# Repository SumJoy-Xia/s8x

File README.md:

# s8x
open source H87/H88 and infinite875 PCB made by sumjoy
开源H87/H88和infinite875 PCB

kicad preview
kicad预览图

firmware to be updated, stay tuned
固件后续更新

PYG.step is the step file of PCB which represents the 3d model of PCB
in case u need it for drawing keyboard cases
PYG.step是PCB的模型
为了方便大家画键盘

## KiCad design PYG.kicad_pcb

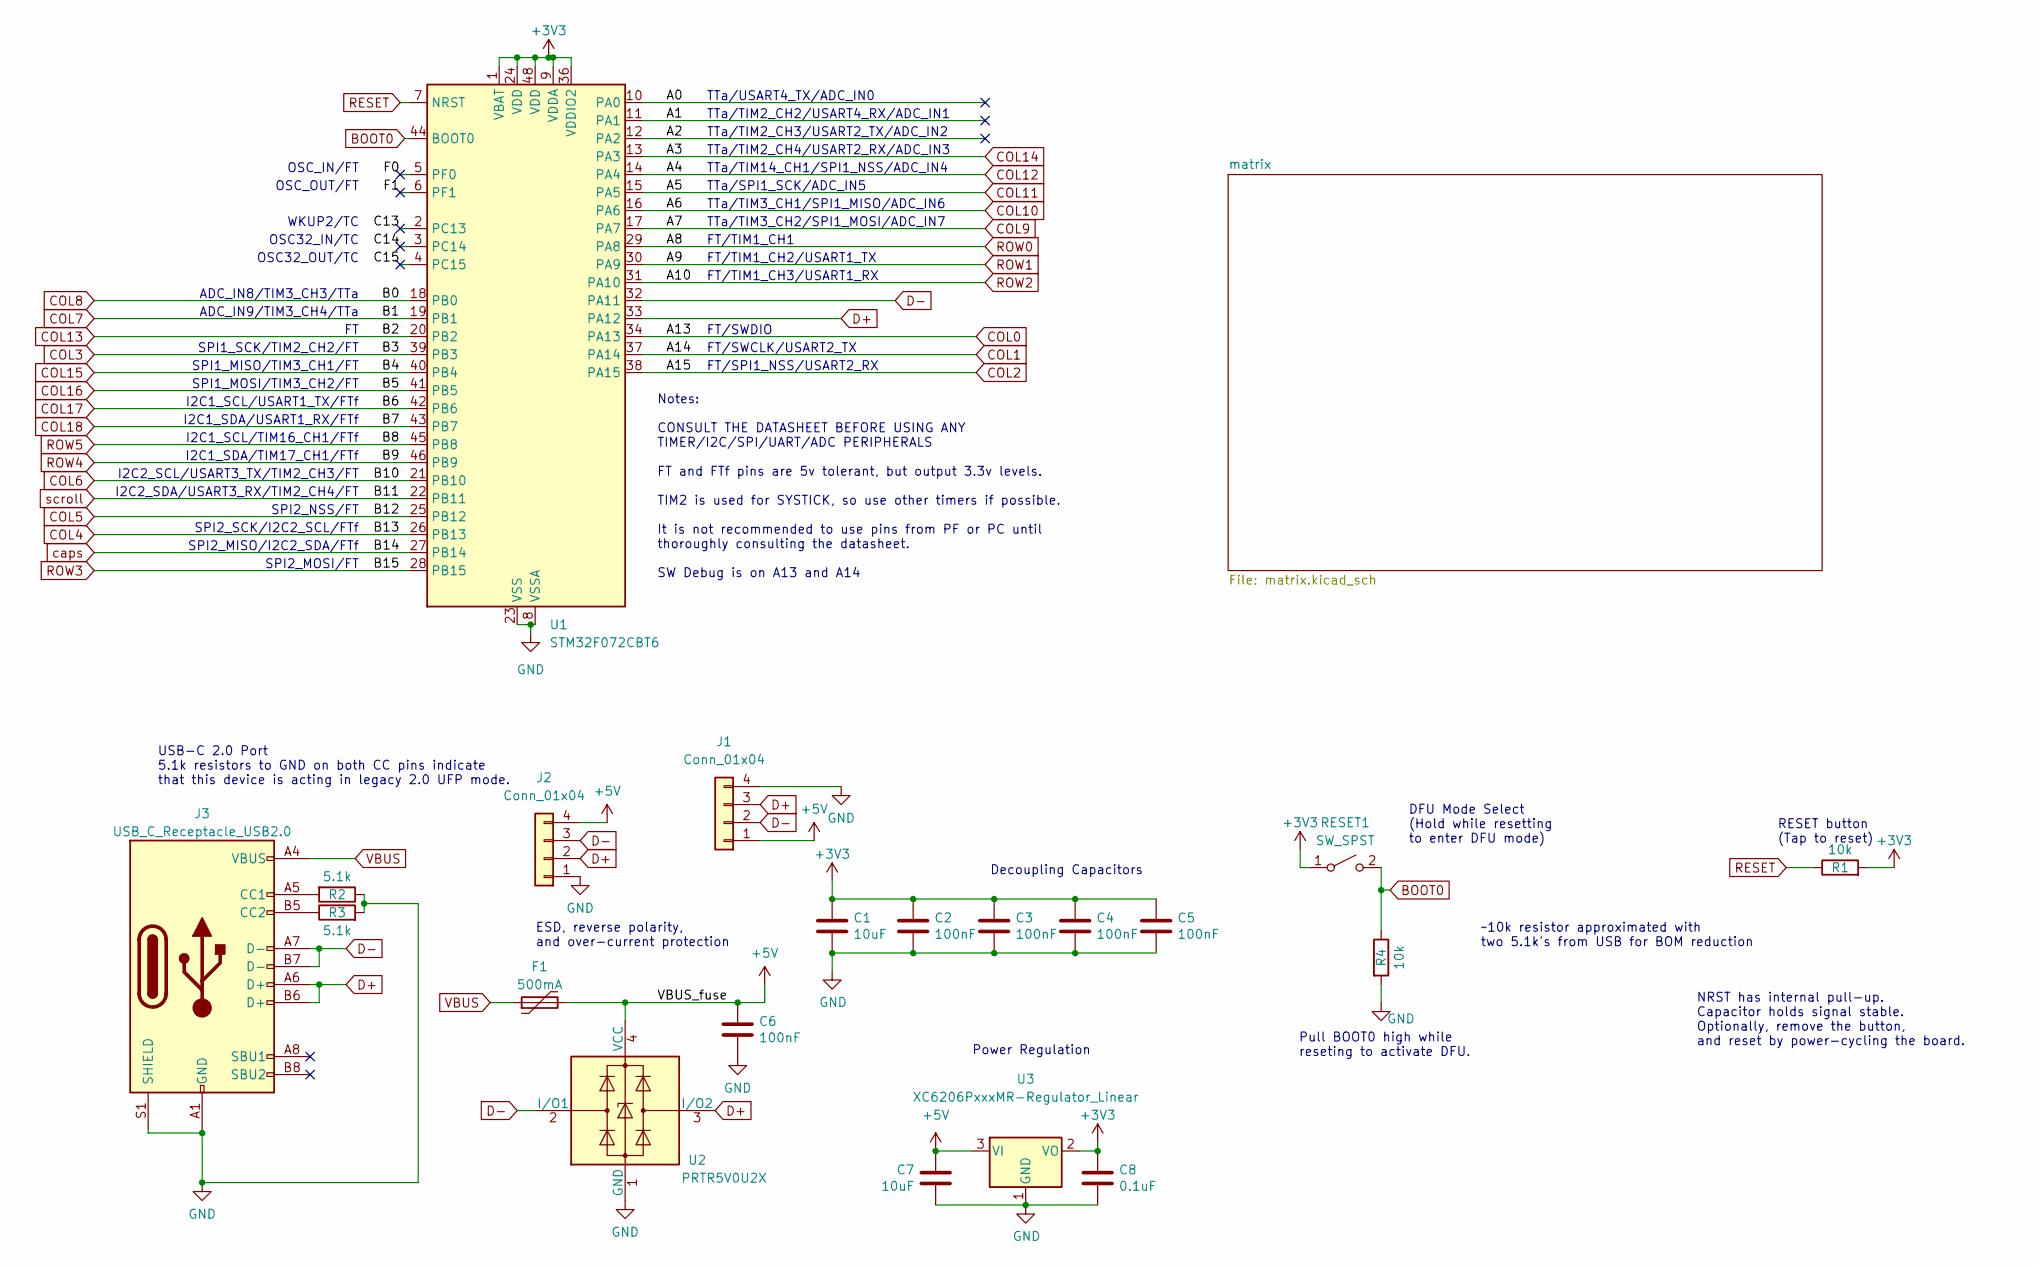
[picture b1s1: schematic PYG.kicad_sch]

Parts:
C1, C7: 10uF; C_0805_2012Metric; LCSC C307331
C2, C3, C4, C5, C6: 100nF; C_0805_2012Metric; LCSC C307331
C8: 0.1uF; C_0805_2012Metric; LCSC C307331
F1: 500mA; Fuse_1206_3216Metric; LCSC C135341
J1: Conn_01x04; JST_SH_SM04B-SRSS-TB_1x04-1MP_P1.00mm_Horizontal
J2: Conn_01x04; PinHeader_1x04_P2.54mm_Vertical
J3: USB_C_Receptacle_USB2.0; USB_C_Receptacle_HRO_TYPE-C-31-M-12; JlcRotOffset 180
R1, R4: 10k; R_0805_2012Metric
R2, R3: 5.1k; R_0805_2012Metric
RESET1: SW_SPST; SW_SPST_TL3342
U1: STM32F072CBT6; LQFP-48_7x7mm_P0.5mm; JlcRotOffset 90
U2: PRTR5V0U2X; SOT-143; LCSC C2827688
U3: XC6206PxxxMR-Regulator_Linear; SOT-23; LCSC C5446

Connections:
+3V3: C1.1, C2.1, C3.1, C4.1, C5.1, C8.1, R1.2, RESET1.1 (A), U1.1 (VBAT), U1.9 (VDDA), U1.24 (VDD), U1.36 (VDDIO2), U1.48 (VDD), U3.2 (VO)
+5V: C6.1, C7.1, F1.2, J1.1, J2.4, U2.4 (VCC), U3.3 (VI); also elsewhere on the board
/A0: U1.10 (PA0)
/A1: U1.11 (PA1)
/A2: U1.12 (PA2)
/C13: U1.2 (PC13)
/C14: U1.3 (PC14)
/C15: U1.4 (PC15)
/F0: U1.5 (PF0)
/F1: U1.6 (PF1)
BOOT0: R4.1, RESET1.2 (B), U1.44 (BOOT0)
COL0: U1.34 (PA13); also elsewhere on the board
COL1: U1.37 (PA14); also elsewhere on the board
COL2: U1.38 (PA15); also elsewhere on the board
COL3: U1.39 (PB3); also elsewhere on the board
COL4: U1.26 (PB13); also elsewhere on the board
COL5: U1.25 (PB12); also elsewhere on the board
COL6: U1.21 (PB10); also elsewhere on the board
COL7: U1.19 (PB1); also elsewhere on the board
COL8: U1.18 (PB0); also elsewhere on the board
COL9: U1.17 (PA7); also elsewhere on the board
COL10: U1.16 (PA6); also elsewhere on the board
COL11: U1.15 (PA5); also elsewhere on the board
COL12: U1.14 (PA4); also elsewhere on the board
COL13: U1.20 (PB2); also elsewhere on the board
COL14: U1.13 (PA3); also elsewhere on the board
COL15: U1.40 (PB4); also elsewhere on the board
COL16: U1.41 (PB5); also elsewhere on the board
COL17: U1.42 (PB6); also elsewhere on the board
COL18: U1.43 (PB7); also elsewhere on the board
D+: J1.3, J2.2, J3.A6 (D+), J3.B6 (D+), U1.33 (PA12), U2.3 (I/O2)
D-: J1.2, J2.3, J3.A7 (D-), J3.B7 (D-), U1.32 (PA11), U2.2 (I/O1)
GND: C1.2, C2.2, C3.2, C4.2, C5.2, C6.2, C7.2, C8.2, J1.4, J2.1, J3.A1 (GND), J3.A12 (GND), J3.B1 (GND), J3.B12 (GND), J3.S1 (SHIELD), R2.1, R3.2, R4.2, U1.8 (VSSA), U1.23 (VSS), U1.35 (VSS), U1.47 (VSS), U2.1 (GND), U3.1 (GND)
unnamed: J3.A5 (CC1), R2.2
unnamed: J3.B5 (CC2), R3.1
RESET: R1.1, U1.7 (NRST)
ROW0: U1.29 (PA8); also elsewhere on the board
ROW1: U1.30 (PA9); also elsewhere on the board
ROW2: U1.31 (PA10); also elsewhere on the board
ROW3: U1.28 (PB15); also elsewhere on the board
ROW4: U1.46 (PB9); also elsewhere on the board
ROW5: U1.45 (PB8); also elsewhere on the board
VBUS: F1.1, J3.A4 (VBUS), J3.A9 (VBUS), J3.B4 (VBUS), J3.B9 (VBUS)
caps: U1.27 (PB14); also elsewhere on the board
scroll: U1.22 (PB11); also elsewhere on the board

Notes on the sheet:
SPI1_SCK/TIM2_CH2/FT
SPI2_MISO/I2C2_SDA/FTf
SPI1_MOSI/TIM3_CH2/FT
Notes: CONSULT THE DATASHEET BEFORE USING ANY TIMER/I2C/SPI/UART/ADC PERIPHERALS FT and FTf pins are 5v tolerant, but output 3.3v levels. TIM2 is used for SYSTICK, so use other timers if possible. It is not recommended to use pins from PF or PC until thoroughly consulting the datasheet. SW Debug is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
TTa/TIM3_CH2/SPI1_MOSI/ADC_IN7
FT/TIM1_CH3/USART1_RX
SPI2_MOSI/FT
I2C1_SDA/USART1_RX/FTf
FT/TIM1_CH1
OSC32_OUT/TC
I2C2_SDA/USART3_RX/TIM2_CH4/FT
SPI2_SCK/I2C2_SCL/FTf
OSC_OUT/FT
SPI2_NSS/FT
TTa/TIM3_CH1/SPI1_MISO/ADC_IN6
SPI1_MISO/TIM3_CH1/FT
I2C1_SDA/TIM17_CH1/FTf
I2C2_SCL/USART3_TX/TIM2_CH3/FT
I2C1_SCL/TIM16_CH1/FTf
ADC_IN8/TIM3_CH3/TTa
WKUP2/TC
TTa/TIM2_CH3/USART2_TX/ADC_IN2
TTa/TIM14_CH1/SPI1_NSS/ADC_IN4
NRST has internal pull-up. Capacitor holds signal stable. Optionally, remove the button, and reset by power-cycling the board.
DFU Mode Select (Hold while resetting to enter DFU mode)
ESD, reverse polarity, and over-current protection
FT/SPI1_NSS/USART2_RX
~10k resistor approximated with two 5.1k's from USB for BOM reduction
FT/SWDIO
TTa/TIM2_CH4/USART2_RX/ADC_IN3
TTa/USART4_TX/ADC_IN0
USB-C 2.0 Port 5.1k resistors to GND on both CC pins indicate that this device is acting in legacy 2.0 UFP mode.
RESET button (Tap to reset)
ADC_IN9/TIM3_CH4/TTa
TTa/SPI1_SCK/ADC_IN5
FT/TIM1_CH2/USART1_TX
Power Regulation
OSC_IN/FT
TTa/TIM2_CH2/USART4_RX/ADC_IN1
Decoupling Capacitors

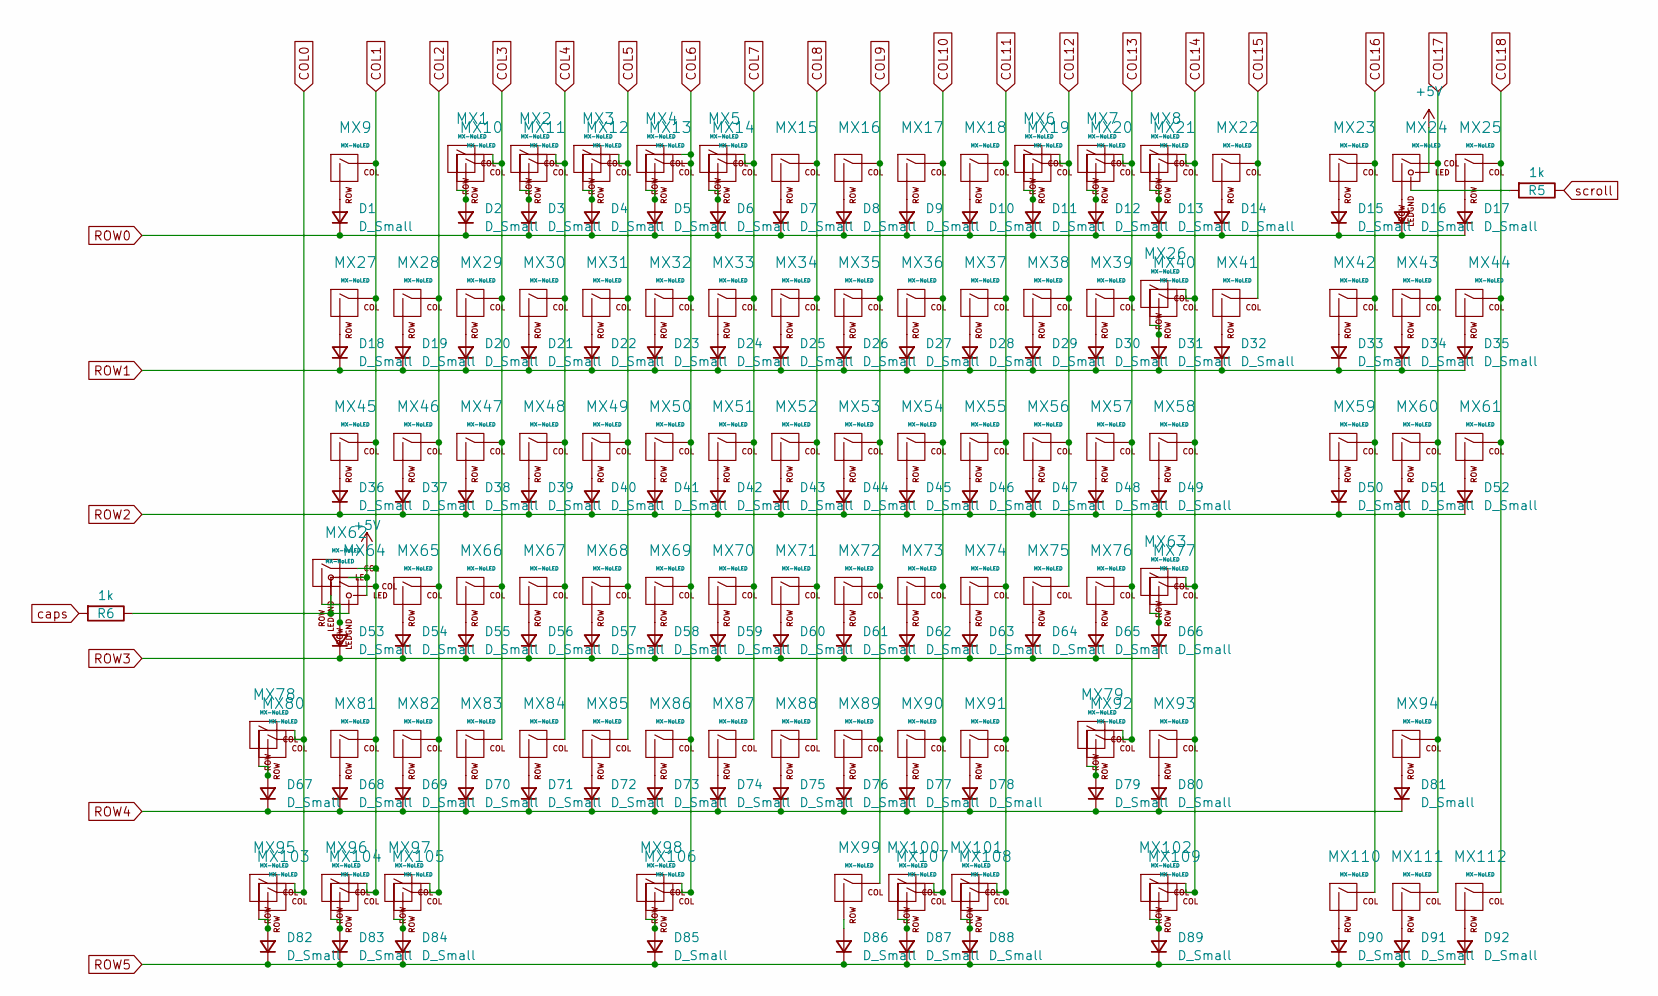
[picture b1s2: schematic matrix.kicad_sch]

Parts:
D1, D2, D3, D4, D5, D6, D7, D8, D9, D10, D11, D12, D13, D14, D15, D16, D17, D18, D19, D20, D21, D22, D23, D24, D25, D26, D27, D28, D29, D30, D31, D32, D33, D34, D35, D36, D37, D38, D39, D40, D41, D42, D43, D44, D45, D46, D47, D48, D49, D50, D51, D52, D53, D54, D55, D56, D57, D58, D59, D60, D61, D62, D63, D64, D65, D66, D67, D68, D69, D70, D71, D72, D73, D74, D75, D76, D77, D78, D79, D80, D81, D82, D83, D84, D85, D86, D87, D88, D89, D90, D91, D92: D_Small; D_0805_2012Metric
MX1, MX2, MX3, MX4, MX5, MX6, MX7, MX8, MX9, MX10, MX11, MX12, MX13, MX14, MX15, MX16, MX17, MX18, MX19, MX20, MX21, MX22, MX23, MX25, MX26, MX27, MX28, MX29, MX30, MX31, MX32, MX33, MX34, MX35, MX36, MX37, MX38, MX39, MX41, MX42, MX43, MX44, MX46, MX47, MX48, MX49, MX50, MX51, MX52, MX53, MX54, MX55, MX56, MX57, MX59, MX60, MX61, MX65, MX66, MX67, MX68, MX69, MX70, MX71, MX72, MX73, MX74, MX75, MX76, MX81, MX82, MX83, MX84, MX85, MX86, MX87, MX88, MX89, MX90, MX91, MX93, MX94, MX104, MX108, MX110, MX111, MX112: MX-NoLED; MXOnly-1U-NoLED
MX24: MX-NoLED; MXOnly-1U
MX40: MX-NoLED; MXOnly-2U-NoLED
MX45, MX58, MX103, MX105, MX107, MX109: MX-NoLED; MXOnly-1.5U-NoLED
MX62: MX-NoLED; MXOnly-1.75U-FLIPPED
MX63: MX-NoLED; MXOnly-ISO-ReversedStabilizers-NoLED
MX64: MX-NoLED; MXOnly-1.75U-STEP1.25
MX77, MX80: MX-NoLED; MXOnly-2.25U-NoLED
MX78, MX95, MX96, MX97, MX99, MX100, MX101, MX102: MX-NoLED; MXOnly-1.25U-NoLED
MX79: MX-NoLED; MXOnly-1.75U-NoLED
MX92: MX-NoLED; MXOnly-2.75U-NoLED
MX98: MX-NoLED; MXOnly-6.25U-ReversedStabilizers-NoLED
MX106: MX-NoLED; MXOnly-7U-ReversedStabilizers-NoLED
R5, R6: 1k; R_0805_2012Metric

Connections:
+5V: MX24.3 (LED), MX62.3 (LED), MX64.3 (LED); also elsewhere on the board
COL0: MX78.1 (COL), MX80.1 (COL), MX95.1 (COL), MX103.1 (COL); also elsewhere on the board
COL1: MX9.1 (COL), MX27.1 (COL), MX45.1 (COL), MX62.1 (COL), MX64.1 (COL), MX81.1 (COL), MX96.1 (COL), MX104.1 (COL); also elsewhere on the board
COL2: MX28.1 (COL), MX46.1 (COL), MX65.1 (COL), MX82.1 (COL), MX97.1 (COL), MX105.1 (COL); also elsewhere on the board
COL3: MX1.1 (COL), MX10.1 (COL), MX29.1 (COL), MX47.1 (COL), MX66.1 (COL), MX83.1 (COL); also elsewhere on the board
COL4: MX2.1 (COL), MX11.1 (COL), MX30.1 (COL), MX48.1 (COL), MX67.1 (COL), MX84.1 (COL); also elsewhere on the board
COL5: MX3.1 (COL), MX12.1 (COL), MX31.1 (COL), MX49.1 (COL), MX68.1 (COL), MX85.1 (COL); also elsewhere on the board
COL6: MX4.1 (COL), MX13.1 (COL), MX32.1 (COL), MX50.1 (COL), MX69.1 (COL), MX86.1 (COL), MX98.1 (COL), MX106.1 (COL); also elsewhere on the board
COL7: MX5.1 (COL), MX14.1 (COL), MX33.1 (COL), MX51.1 (COL), MX70.1 (COL), MX87.1 (COL); also elsewhere on the board
COL8: MX15.1 (COL), MX34.1 (COL), MX52.1 (COL), MX71.1 (COL), MX88.1 (COL); also elsewhere on the board
COL9: MX16.1 (COL), MX35.1 (COL), MX53.1 (COL), MX72.1 (COL), MX89.1 (COL), MX99.1 (COL); also elsewhere on the board
COL10: MX17.1 (COL), MX36.1 (COL), MX54.1 (COL), MX73.1 (COL), MX90.1 (COL), MX100.1 (COL), MX107.1 (COL); also elsewhere on the board
COL11: MX18.1 (COL), MX37.1 (COL), MX55.1 (COL), MX74.1 (COL), MX91.1 (COL), MX101.1 (COL), MX108.1 (COL); also elsewhere on the board
COL12: MX6.1 (COL), MX19.1 (COL), MX38.1 (COL), MX56.1 (COL), MX75.1 (COL); also elsewhere on the board
COL13: MX7.1 (COL), MX20.1 (COL), MX39.1 (COL), MX57.1 (COL), MX76.1 (COL), MX79.1 (COL), MX92.1 (COL); also elsewhere on the board
COL14: MX8.1 (COL), MX21.1 (COL), MX26.1 (COL), MX40.1 (COL), MX58.1 (COL), MX63.1 (COL), MX77.1 (COL), MX93.1 (COL), MX102.1 (COL), MX109.1 (COL); also elsewhere on the board
COL15: MX22.1 (COL), MX41.1 (COL); also elsewhere on the board
COL16: MX23.1 (COL), MX42.1 (COL), MX59.1 (COL), MX110.1 (COL); also elsewhere on the board
COL17: MX24.1 (COL), MX43.1 (COL), MX60.1 (COL), MX94.1 (COL), MX111.1 (COL); also elsewhere on the board
COL18: MX25.1 (COL), MX44.1 (COL), MX61.1 (COL), MX112.1 (COL); also elsewhere on the board
unnamed: D1.2 (A), MX9.2 (ROW)
unnamed: D2.2 (A), MX1.2 (ROW), MX10.2 (ROW)
unnamed: D3.2 (A), MX2.2 (ROW), MX11.2 (ROW)
unnamed: D4.2 (A), MX3.2 (ROW), MX12.2 (ROW)
unnamed: D5.2 (A), MX4.2 (ROW), MX13.2 (ROW)
unnamed: D6.2 (A), MX5.2 (ROW), MX14.2 (ROW)
unnamed: D7.2 (A), MX15.2 (ROW)
unnamed: D8.2 (A), MX16.2 (ROW)
unnamed: D9.2 (A), MX17.2 (ROW)
unnamed: D10.2 (A), MX18.2 (ROW)
unnamed: D11.2 (A), MX6.2 (ROW), MX19.2 (ROW)
unnamed: D12.2 (A), MX7.2 (ROW), MX20.2 (ROW)
unnamed: D13.2 (A), MX8.2 (ROW), MX21.2 (ROW)
unnamed: D14.2 (A), MX22.2 (ROW)
unnamed: D15.2 (A), MX23.2 (ROW)
unnamed: D16.2 (A), MX24.2 (ROW)
unnamed: D17.2 (A), MX25.2 (ROW)
unnamed: D18.2 (A), MX27.2 (ROW)
unnamed: D19.2 (A), MX28.2 (ROW)
unnamed: D20.2 (A), MX29.2 (ROW)
unnamed: D21.2 (A), MX30.2 (ROW)
unnamed: D22.2 (A), MX31.2 (ROW)
unnamed: D23.2 (A), MX32.2 (ROW)
unnamed: D24.2 (A), MX33.2 (ROW)
unnamed: D25.2 (A), MX34.2 (ROW)
unnamed: D26.2 (A), MX35.2 (ROW)
unnamed: D27.2 (A), MX36.2 (ROW)
unnamed: D28.2 (A), MX37.2 (ROW)
unnamed: D29.2 (A), MX38.2 (ROW)
unnamed: D30.2 (A), MX39.2 (ROW)
unnamed: D31.2 (A), MX26.2 (ROW), MX40.2 (ROW)
unnamed: D32.2 (A), MX41.2 (ROW)
unnamed: D33.2 (A), MX42.2 (ROW)
unnamed: D34.2 (A), MX43.2 (ROW)
unnamed: D35.2 (A), MX44.2 (ROW)
unnamed: D36.2 (A), MX45.2 (ROW)
unnamed: D37.2 (A), MX46.2 (ROW)
unnamed: D38.2 (A), MX47.2 (ROW)
unnamed: D39.2 (A), MX48.2 (ROW)
unnamed: D40.2 (A), MX49.2 (ROW)
unnamed: D41.2 (A), MX50.2 (ROW)
unnamed: D42.2 (A), MX51.2 (ROW)
unnamed: D43.2 (A), MX52.2 (ROW)
unnamed: D44.2 (A), MX53.2 (ROW)
unnamed: D45.2 (A), MX54.2 (ROW)
unnamed: D46.2 (A), MX55.2 (ROW)
unnamed: D47.2 (A), MX56.2 (ROW)
unnamed: D48.2 (A), MX57.2 (ROW)
unnamed: D49.2 (A), MX58.2 (ROW)
unnamed: D50.2 (A), MX59.2 (ROW)
unnamed: D51.2 (A), MX60.2 (ROW)
unnamed: D52.2 (A), MX61.2 (ROW)
unnamed: D53.2 (A), MX62.2 (ROW), MX64.2 (ROW)
unnamed: D54.2 (A), MX65.2 (ROW)
unnamed: D55.2 (A), MX66.2 (ROW)
unnamed: D56.2 (A), MX67.2 (ROW)
unnamed: D57.2 (A), MX68.2 (ROW)
unnamed: D58.2 (A), MX69.2 (ROW)
unnamed: D59.2 (A), MX70.2 (ROW)
unnamed: D60.2 (A), MX71.2 (ROW)
unnamed: D61.2 (A), MX72.2 (ROW)
unnamed: D62.2 (A), MX73.2 (ROW)
unnamed: D63.2 (A), MX74.2 (ROW)
unnamed: D64.2 (A), MX75.2 (ROW)
unnamed: D65.2 (A), MX76.2 (ROW)
unnamed: D66.2 (A), MX63.2 (ROW), MX77.2 (ROW)
unnamed: D67.2 (A), MX78.2 (ROW), MX80.2 (ROW)
unnamed: D68.2 (A), MX81.2 (ROW)
unnamed: D69.2 (A), MX82.2 (ROW)
unnamed: D70.2 (A), MX83.2 (ROW)
unnamed: D71.2 (A), MX84.2 (ROW)
unnamed: D72.2 (A), MX85.2 (ROW)
unnamed: D73.2 (A), MX86.2 (ROW)
unnamed: D74.2 (A), MX87.2 (ROW)
unnamed: D75.2 (A), MX88.2 (ROW)
unnamed: D76.2 (A), MX89.2 (ROW)
unnamed: D77.2 (A), MX90.2 (ROW)
unnamed: D78.2 (A), MX91.2 (ROW)
unnamed: D79.2 (A), MX79.2 (ROW), MX92.2 (ROW)
unnamed: D80.2 (A), MX93.2 (ROW)
unnamed: D81.2 (A), MX94.2 (ROW)
unnamed: D82.2 (A), MX95.2 (ROW), MX103.2 (ROW)
unnamed: D83.2 (A), MX96.2 (ROW), MX104.2 (ROW)
unnamed: D84.2 (A), MX97.2 (ROW), MX105.2 (ROW)
unnamed: D85.2 (A), MX98.2 (ROW), MX106.2 (ROW)
unnamed: D86.2 (A), MX99.2 (ROW)
unnamed: D87.2 (A), MX100.2 (ROW), MX107.2 (ROW)
unnamed: D88.2 (A), MX101.2 (ROW), MX108.2 (ROW)
unnamed: D89.2 (A), MX102.2 (ROW), MX109.2 (ROW)
unnamed: D90.2 (A), MX110.2 (ROW)
unnamed: D91.2 (A), MX111.2 (ROW)
unnamed: D92.2 (A), MX112.2 (ROW)
unnamed: MX24.4 (LEDGND), R5.2
unnamed: MX62.4 (LEDGND), MX64.4 (LEDGND), R6.1
ROW0: D1.1 (K), D2.1 (K), D3.1 (K), D4.1 (K), D5.1 (K), D6.1 (K), D7.1 (K), D8.1 (K), D9.1 (K), D10.1 (K), D11.1 (K), D12.1 (K), D13.1 (K), D14.1 (K), D15.1 (K), D16.1 (K), D17.1 (K); also elsewhere on the board
ROW1: D18.1 (K), D19.1 (K), D20.1 (K), D21.1 (K), D22.1 (K), D23.1 (K), D24.1 (K), D25.1 (K), D26.1 (K), D27.1 (K), D28.1 (K), D29.1 (K), D30.1 (K), D31.1 (K), D32.1 (K), D33.1 (K), D34.1 (K), D35.1 (K); also elsewhere on the board
ROW2: D36.1 (K), D37.1 (K), D38.1 (K), D39.1 (K), D40.1 (K), D41.1 (K), D42.1 (K), D43.1 (K), D44.1 (K), D45.1 (K), D46.1 (K), D47.1 (K), D48.1 (K), D49.1 (K), D50.1 (K), D51.1 (K), D52.1 (K); also elsewhere on the board
ROW3: D53.1 (K), D54.1 (K), D55.1 (K), D56.1 (K), D57.1 (K), D58.1 (K), D59.1 (K), D60.1 (K), D61.1 (K), D62.1 (K), D63.1 (K), D64.1 (K), D65.1 (K), D66.1 (K); also elsewhere on the board
ROW4: D67.1 (K), D68.1 (K), D69.1 (K), D70.1 (K), D71.1 (K), D72.1 (K), D73.1 (K), D74.1 (K), D75.1 (K), D76.1 (K), D77.1 (K), D78.1 (K), D79.1 (K), D80.1 (K), D81.1 (K); also elsewhere on the board
ROW5: D82.1 (K), D83.1 (K), D84.1 (K), D85.1 (K), D86.1 (K), D87.1 (K), D88.1 (K), D89.1 (K), D90.1 (K), D91.1 (K), D92.1 (K); also elsewhere on the board
caps: R6.2; also elsewhere on the board
scroll: R5.1; also elsewhere on the board

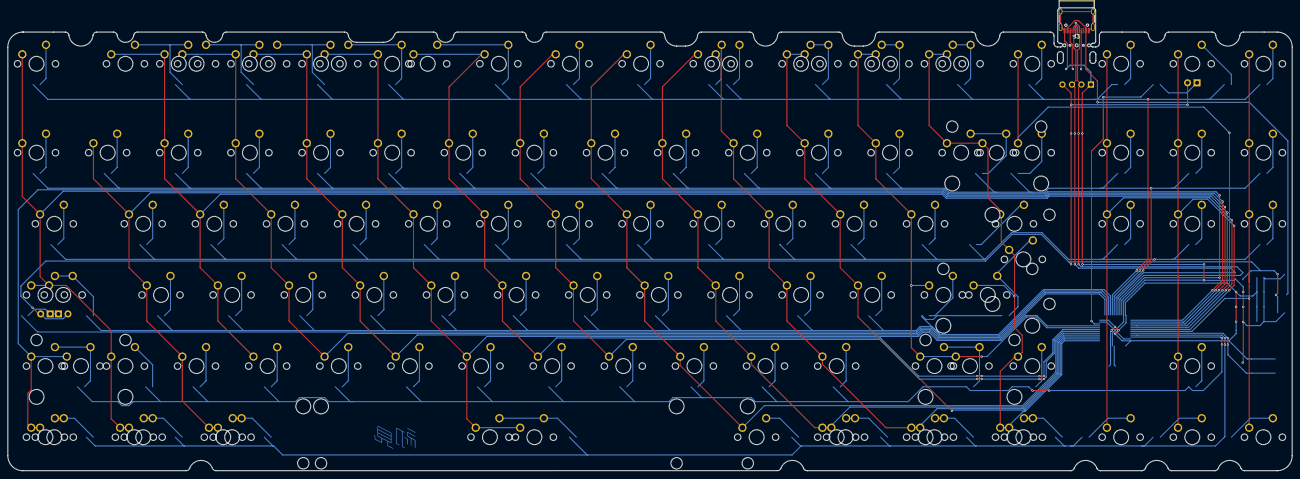
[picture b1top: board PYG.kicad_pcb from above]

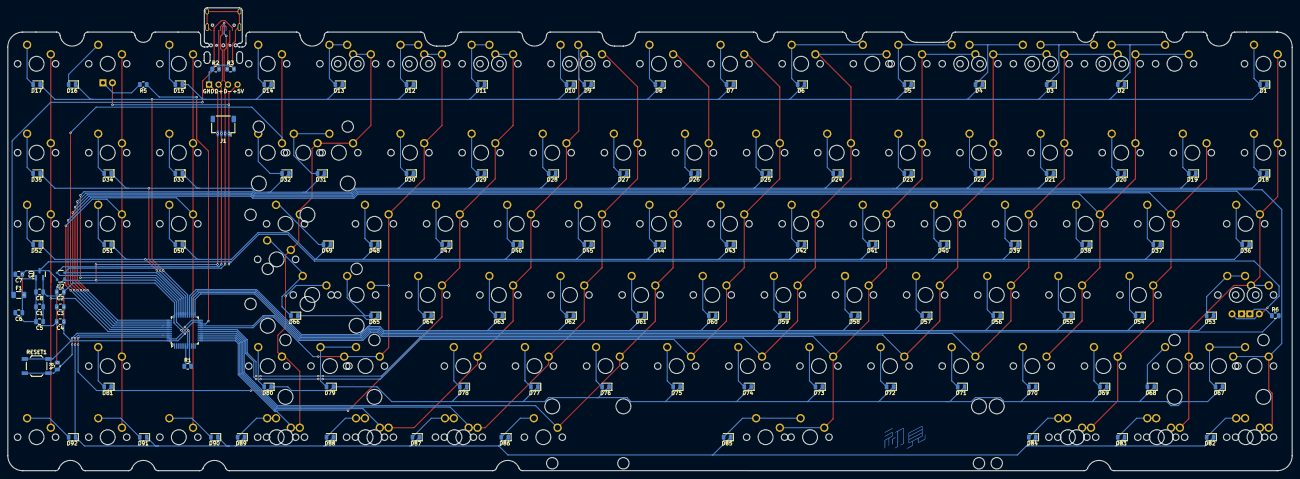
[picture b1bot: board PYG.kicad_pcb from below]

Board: 2 copper layers, 344.0 x 124.0 mm, 226 parts (112 on the bottom side), 131 nets.
